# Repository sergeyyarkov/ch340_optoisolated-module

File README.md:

# CH340 Optoisolated module

This circuit is enough for 4800bps. Use high-speed optocouplers to improve speed performance.

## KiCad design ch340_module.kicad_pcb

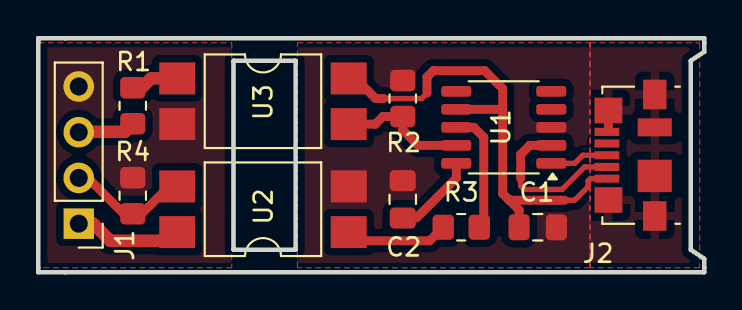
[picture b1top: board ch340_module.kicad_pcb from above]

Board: 2 copper layers, 37.0 x 13.0 mm, 11 parts (0 on the bottom side), 13 nets.

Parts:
C1, C2: 0.1uF; C_0805_2012Metric_Pad1.18x1.45mm_HandSolder
J1: UART Device; PinHeader_1x04_P2.54mm_Vertical
J2: USB; USB_Micro-B_Molex_47346-0001
R1, R3: 330; R_0805_2012Metric_Pad1.20x1.40mm_HandSolder
R2, R4: 10K; R_0805_2012Metric_Pad1.20x1.40mm_HandSolder
U1: CH340K; SSOP-10-1EP_3.9x4.9mm_P1mm_EP2.1x3.3mm
U2, U3: LTV-817S; SMDIP-4_W9.53mm

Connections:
+5V: J1.1, U2.4
/RX: J1.2, R4.2, U2.3
/TX: J1.3, R1.2
GND1: J1.4, R4.1, U3.2
GND2: C1.2, C2.1, J2.5 (GND), J2.6 (Shield), R2.2, U1.3 (GND), U2.2
unnamed: J2.3 (D+), U1.1 (UD+)
unnamed: J2.2 (D-), U1.2 (UD-)
unnamed: R1.1, U3.1
unnamed: R3.2, U2.1
unnamed: R2.1, U1.9 (RXD), U3.3
unnamed: R3.1, U1.8 (TXD)
unnamed: C2.2, U1.10 (V3)
VCC: C1.1, J2.1 (VBUS), U1.7 (VCC), U3.4

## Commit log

2024-12-30 done
2024-12-30 readme
